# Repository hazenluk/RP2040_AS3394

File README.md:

# RP2040_AS3394
An AS3394 Voice Card controlled by RP2040.

Schematics and Routing in KiCad. Uses 30Khz PWM with 12-bit duty cycle and 1KHz Low Pass filtering to produce control voltages.

Mainly a way for me to learn and experiment with discrete Sallen-Key and MFB filters. Also a way to avoid out-of-stock DACs during the chip shortage.

Work-In-Progress photo of board:

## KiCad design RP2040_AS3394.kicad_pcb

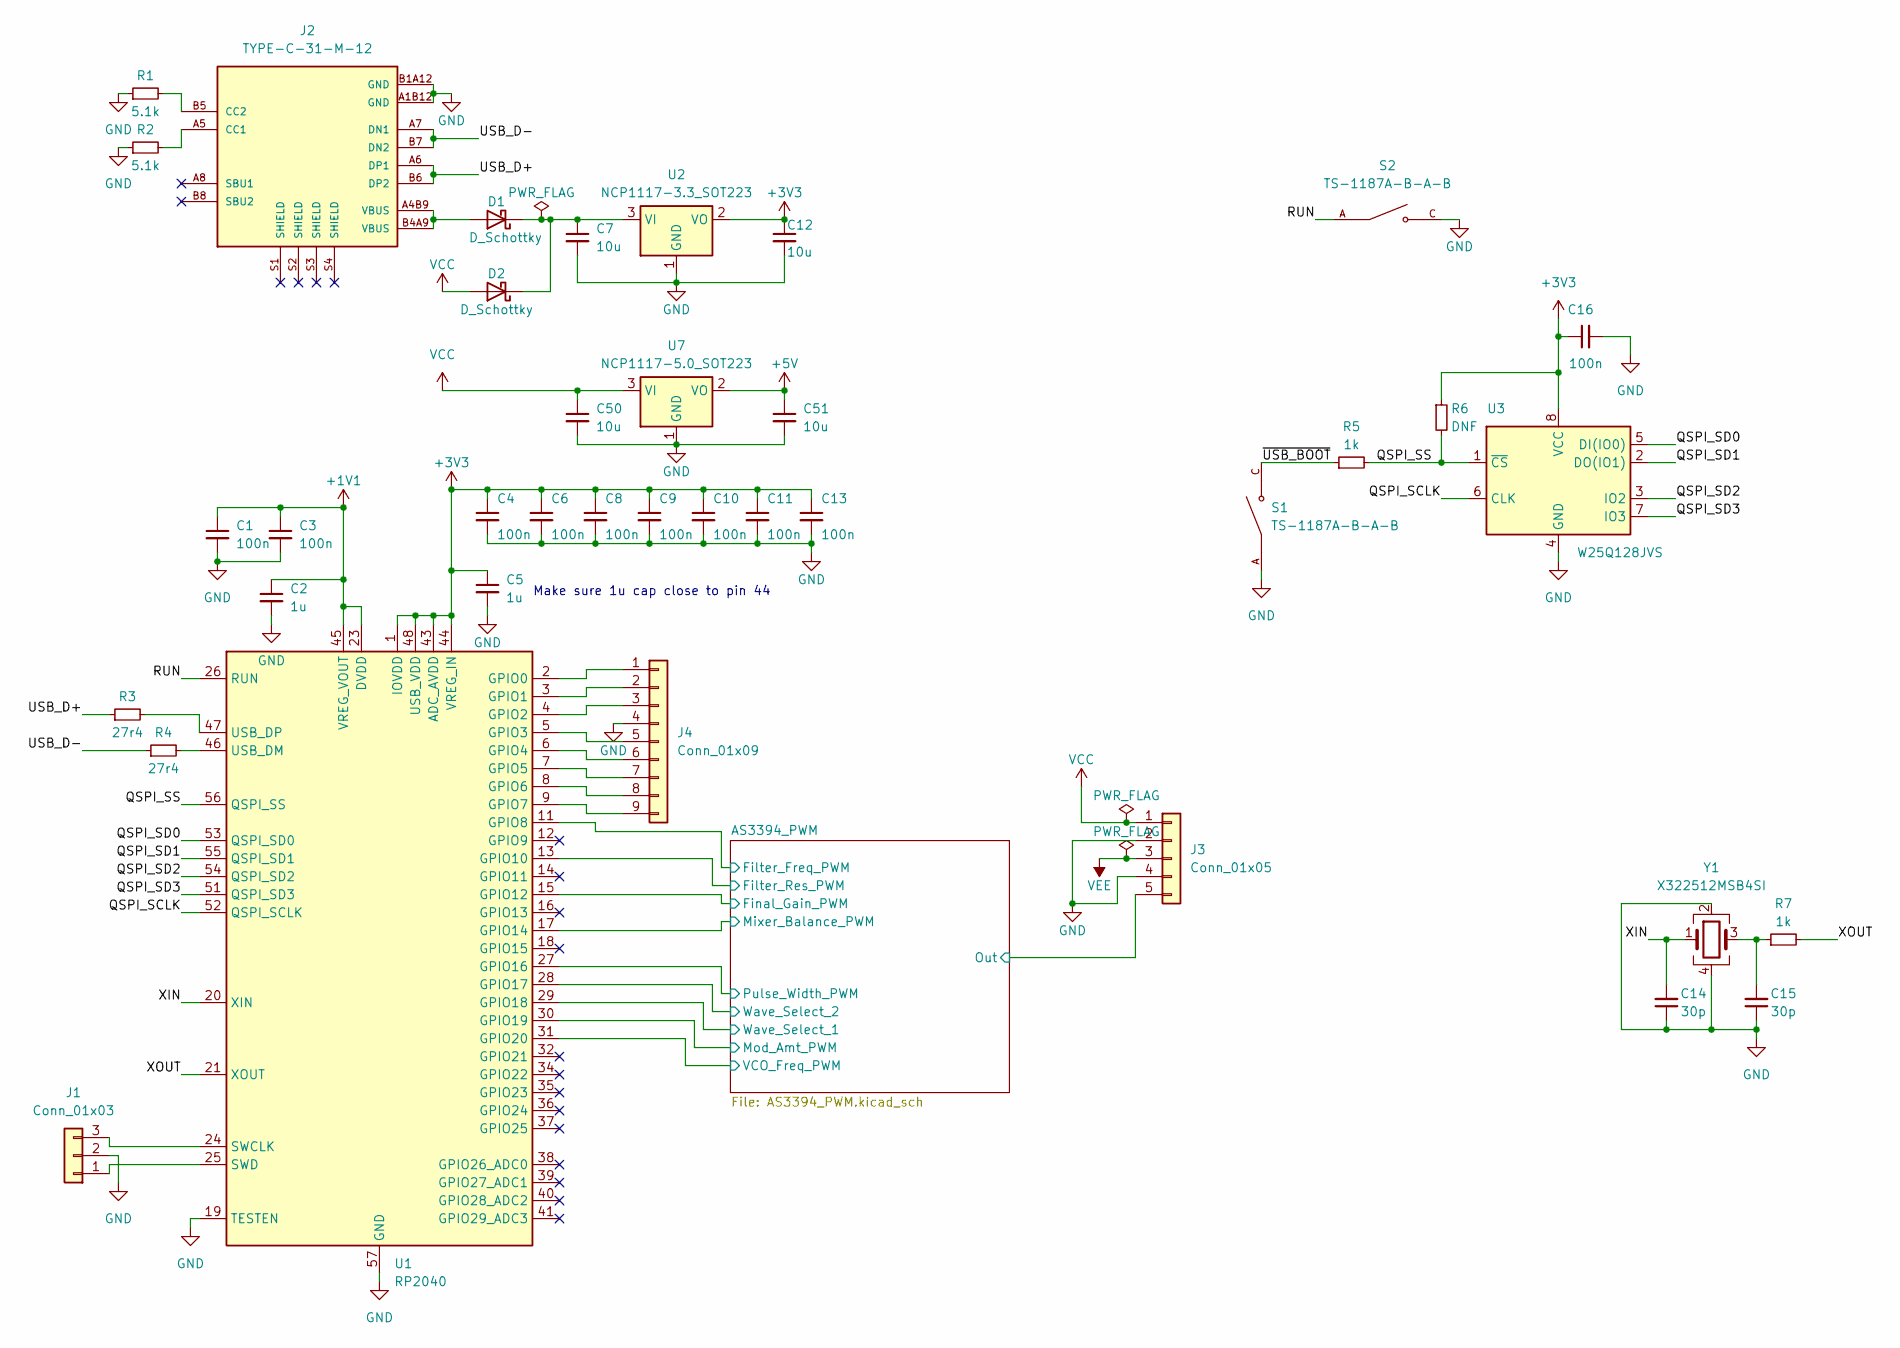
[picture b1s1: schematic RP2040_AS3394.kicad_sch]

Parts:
C1, C3, C4, C6, C8, C9, C10, C11, C13: 100n; C_0402_1005Metric
C2, C5: 1u; C_0402_1005Metric
C7, C12, C50, C51: 10u; C_0603_1608Metric
C14, C15: 30p; C_0402_1005Metric
C16: 100n; C_0603_1608Metric
D1, D2: D_Schottky; D_SMA
J1: Conn_01x03; PinHeader_1x03_P2.54mm_Vertical
J2: TYPE-C-31-M-12; HRO_TYPE-C-31-M-12; PARTREV A
J3: Conn_01x05; PinHeader_1x05_P2.54mm_Vertical
J4: Conn_01x09; PinHeader_1x09_P2.54mm_Vertical
R1, R2: 5.1k; R_0402_1005Metric
R3, R4: 27r4; R_0402_1005Metric
R5, R7: 1k; R_0402_1005Metric
R6: DNF; R_0402_1005Metric
S1, S2: TS-1187A-B-A-B; SW_TS-1187A-B-A-B; PARTREV A0
U1: RP2040; QFN-56-1EP_7x7mm_P0.4mm_EP3.2x3.2mm
U2: NCP1117-3.3_SOT223; SOT-223-3_TabPin2
U3: W25Q128JVS; SOIC-8_5.23x5.23mm_P1.27mm
U7: NCP1117-5.0_SOT223; SOT-223-3_TabPin2
Y1: X322512MSB4SI; Crystal_SMD_3225-4Pin_3.2x2.5mm

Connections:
+1V1: C1.1, C2.1, C3.1, U1.23 (DVDD), U1.45 (VREG_VOUT), U1.50 (DVDD)
+3V3: C4.1, C5.1, C6.1, C8.1, C9.1, C10.1, C11.1, C12.1, C13.1, C16.1, R6.1, U1.1 (IOVDD), U1.10 (IOVDD), U1.22 (IOVDD), U1.33 (IOVDD), U1.42 (IOVDD), U1.43 (ADC_AVDD), U1.44 (VREG_IN), U1.48 (USB_VDD), U1.49 (IOVDD), U2.2 (VO), U3.8 (VCC)
+5V: C51.1, U7.2 (VO); also elsewhere on the board
/AS3394_PWM/Filter_Freq_PWM: U1.11 (GPIO8); also elsewhere on the board
/AS3394_PWM/Filter_Res_PWM: U1.13 (GPIO10); also elsewhere on the board
/AS3394_PWM/Final_Gain_PWM: U1.15 (GPIO12); also elsewhere on the board
/AS3394_PWM/Mixer_Balance_PWM: U1.17 (GPIO14); also elsewhere on the board
/AS3394_PWM/Mod_Amt_PWM: U1.30 (GPIO19); also elsewhere on the board
/AS3394_PWM/Out: J3.5; also elsewhere on the board
/AS3394_PWM/Pulse_Width_PWM: U1.27 (GPIO16); also elsewhere on the board
/AS3394_PWM/VCO_Freq_PWM: U1.31 (GPIO20); also elsewhere on the board
/AS3394_PWM/Wave_Select_1: U1.29 (GPIO18); also elsewhere on the board
/AS3394_PWM/Wave_Select_2: U1.28 (GPIO17); also elsewhere on the board
/QSPI_SCLK: U1.52 (QSPI_SCLK), U3.6 (CLK)
/QSPI_SD0: U1.53 (QSPI_SD0), U3.5 (DI(IO0))
/QSPI_SD1: U1.55 (QSPI_SD1), U3.2 (DO(IO1))
/QSPI_SD2: U1.54 (QSPI_SD2), U3.3 (IO2)
/QSPI_SD3: U1.51 (QSPI_SD3), U3.7 (IO3)
/QSPI_SS: R5.2, R6.2, U1.56 (QSPI_SS), U3.1 (~CS)
/RUN: S2.A, S2.B, U1.26 (RUN)
/USB_D+: J2.A6 (DP1), J2.B6 (DP2), R3.1
/USB_D-: J2.A7 (DN1), J2.B7 (DN2), R4.1
/XIN: C14.2, U1.20 (XIN), Y1.1
/XOUT: R7.2, U1.21 (XOUT)
/~USB_BOOT: R5.1, S1.C, S1.D
GND: C1.2, C2.2, C3.2, C4.2, C5.2, C6.2, C7.2, C8.2, C9.2, C10.2, C11.2, C12.2, C13.2, C14.1, C15.1, C16.2, C50.2, C51.2, J1.2, J2.A1B12 (GND), J2.B1A12 (GND), J3.2, J3.4, J4.4, R1.1, R2.1, S1.A, S1.B, S2.C, S2.D, U1.19 (TESTEN), U1.57 (GND), U2.1 (GND), U3.4 (GND), U7.1 (GND), Y1.2, Y1.4; also elsewhere on the board
unnamed: C15.2, R7.1, Y1.3
unnamed: D1.2 (A), J2.A4B9 (VBUS), J2.B4A9 (VBUS)
unnamed: C7.1, D1.1 (K), D2.1 (K), U2.3 (VI)
unnamed: J1.1, U1.25 (SWD)
unnamed: J1.3, U1.24 (SWCLK)
unnamed: J2.A5 (CC1), R2.2
unnamed: J2.B5 (CC2), R1.2
unnamed: J4.1, U1.2 (GPIO0)
unnamed: J4.2, U1.3 (GPIO1)
unnamed: J4.3, U1.4 (GPIO2)
unnamed: J4.5, U1.5 (GPIO3)
unnamed: J4.6, U1.6 (GPIO4)
unnamed: J4.7, U1.7 (GPIO5)
unnamed: J4.8, U1.8 (GPIO6)
unnamed: J4.9, U1.9 (GPIO7)
unnamed: R4.2, U1.46 (USB_DM)
unnamed: R3.2, U1.47 (USB_DP)
VCC: C50.1, D2.2 (A), J3.1, U7.3 (VI); also elsewhere on the board
VEE: J3.3; also elsewhere on the board

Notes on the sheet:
Make sure 1u cap close to pin 44

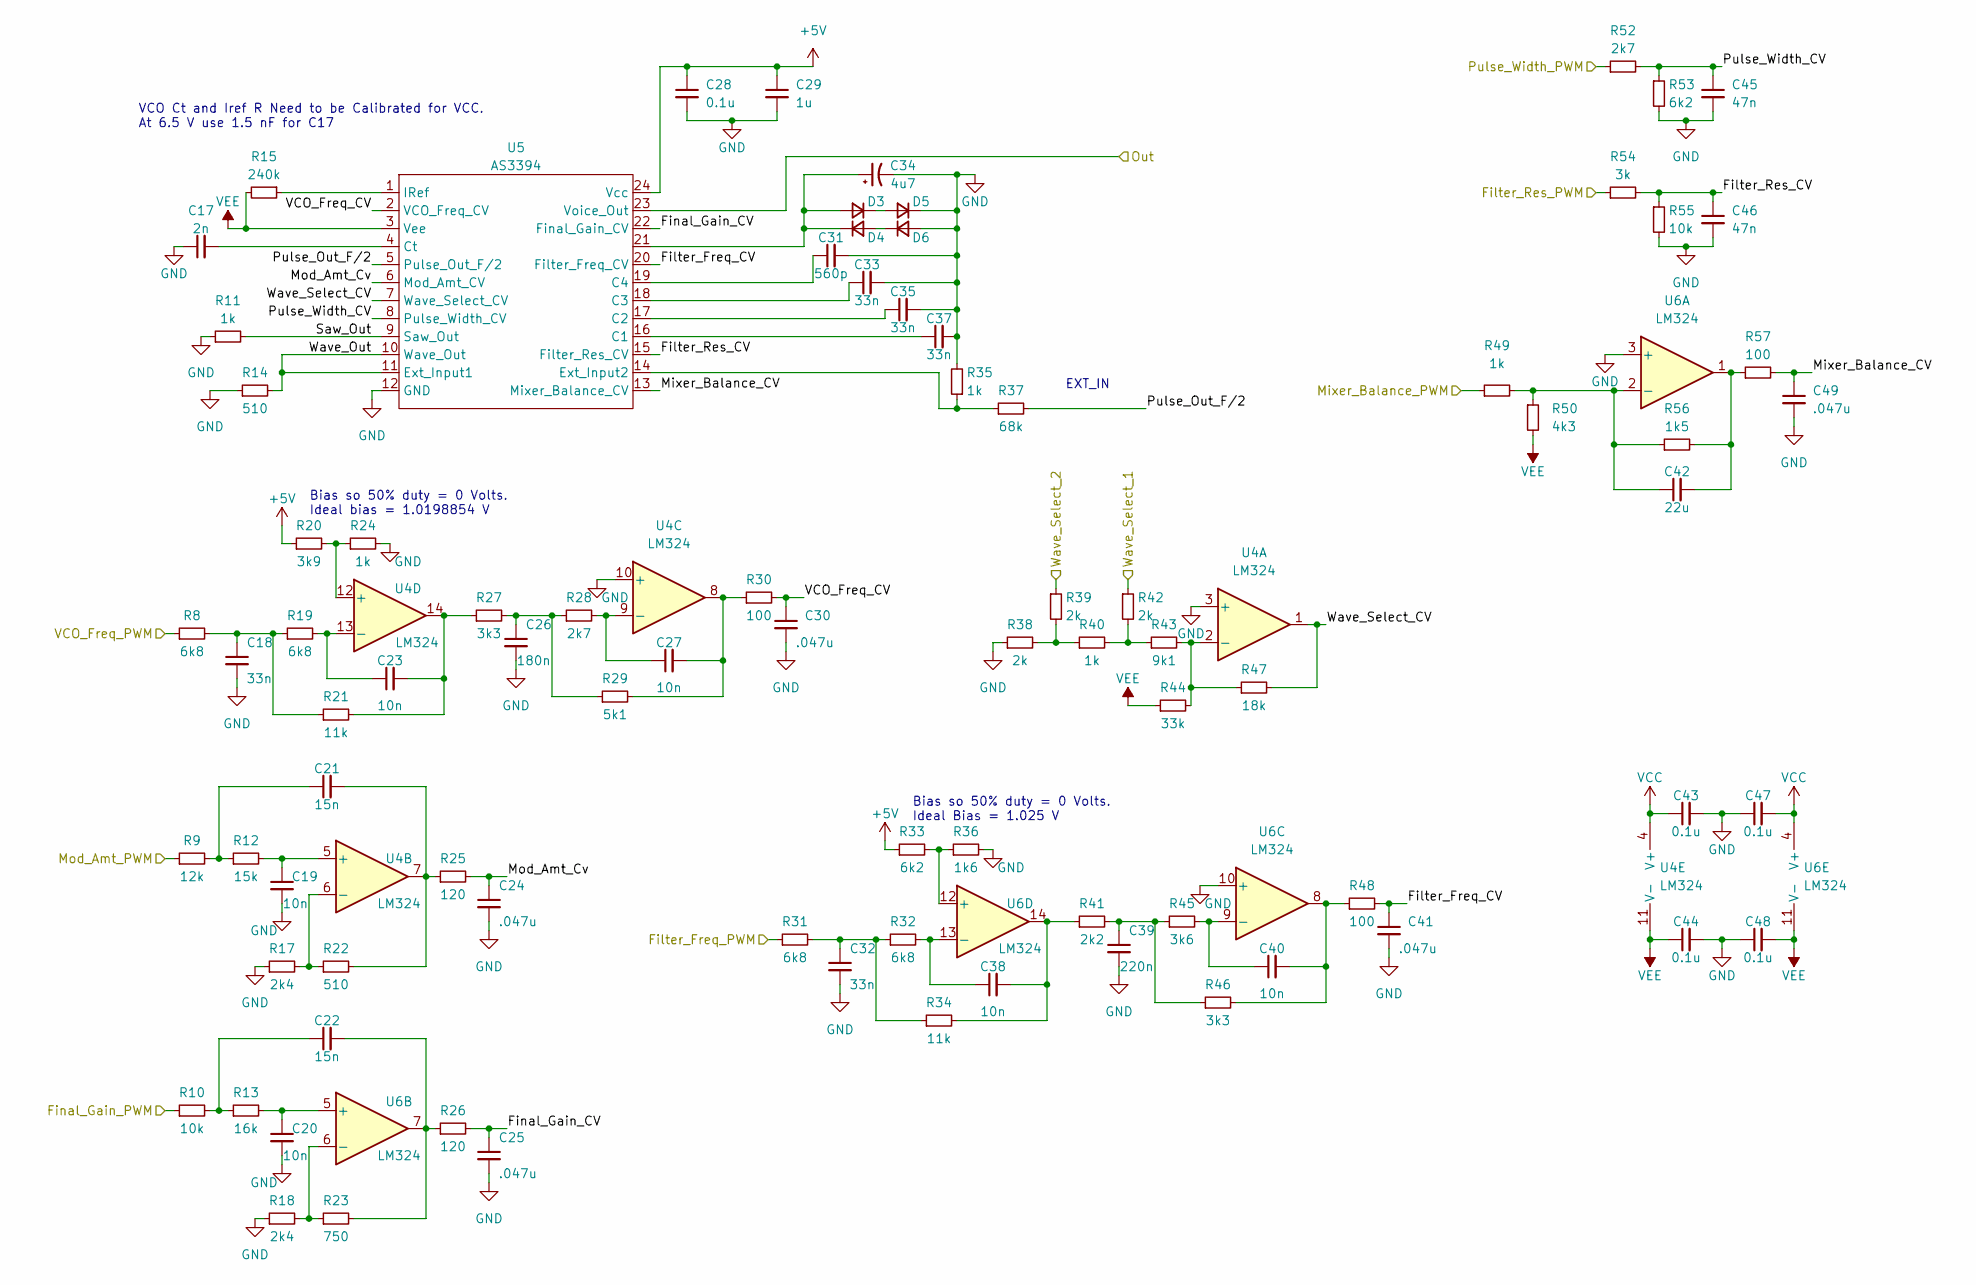
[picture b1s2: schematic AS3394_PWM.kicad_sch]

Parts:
C17: 2n; C_0603_1608Metric
C18, C32, C33, C35, C37: 33n; C_0603_1608Metric
C19, C20, C23, C27, C38, C40: 10n; C_0402_1005Metric
C21, C22: 15n; C_0603_1608Metric
C24, C25, C30, C41, C49: .047u; C_0603_1608Metric
C26: 180n; C_0805_2012Metric
C28, C43, C44, C47, C48: 0.1u; C_0402_1005Metric
C29: 1u; C_0402_1005Metric
C31: 560p; C_0402_1005Metric
C34: 4u7; CP_Elec_4x5.4
C39: 220n; C_0402_1005Metric
C42: 22u; C_1206_3216Metric
C45, C46: 47n; C_0603_1608Metric
D3, D4, D5, D6: D_Small; D_SOD-123
R8, R19, R31, R32: 6k8; R_0402_1005Metric
R9: 12k; R_0402_1005Metric
R10, R55: 10k; R_0402_1005Metric
R11, R24, R35, R40, R49: 1k; R_0402_1005Metric
R12: 15k; R_0402_1005Metric
R13: 16k; R_0805_2012Metric
R14, R22: 510; R_0402_1005Metric
R15: 240k; R_0603_1608Metric
R17, R18: 2k4; R_0402_1005Metric
R20: 3k9; R_0402_1005Metric
R21, R34: 11k; R_0603_1608Metric
R23: 750; R_0603_1608Metric
R25, R26: 120; R_0402_1005Metric
R27, R46: 3k3; R_0402_1005Metric
R28, R52: 2k7; R_0603_1608Metric
R29: 5k1; R_0402_1005Metric
R30, R48, R57: 100; R_0402_1005Metric
R33, R53: 6k2; R_0603_1608Metric
R36: 1k6; R_0402_1005Metric
R37: 68k; R_0402_1005Metric
R38, R39, R42: 2k; R_0402_1005Metric
R41: 2k2; R_0402_1005Metric
R43: 9k1; R_0603_1608Metric
R44: 33k; R_0402_1005Metric
R45: 3k6; R_0603_1608Metric
R47: 18k; R_0402_1005Metric
R50: 4k3; R_0603_1608Metric
R54: 3k; R_0603_1608Metric
R56: 1k5; R_0402_1005Metric
U4, U6: LM324; SOIC-14_3.9x8.7mm_P1.27mm
U5: AS3394; DIP-24_W7.62mm_Socket

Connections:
+5V: C28.1, C29.1, R20.1, R33.1, U5.24 (Vcc); also elsewhere on the board
/AS3394_PWM/Filter_Freq_CV: C41.1, R48.2, U5.20 (Filter_Freq_CV)
/AS3394_PWM/Filter_Freq_PWM: R31.1; also elsewhere on the board
/AS3394_PWM/Filter_Res_CV: C46.1, R54.2, R55.1, U5.15 (Filter_Res_CV)
/AS3394_PWM/Filter_Res_PWM: R54.1; also elsewhere on the board
/AS3394_PWM/Final_Gain_CV: C25.1, R26.2, U5.22 (Final_Gain_CV)
/AS3394_PWM/Final_Gain_PWM: R10.1; also elsewhere on the board
/AS3394_PWM/Mixer_Balance_CV: C49.1, R57.2, U5.13 (Mixer_Balance_CV)
/AS3394_PWM/Mixer_Balance_PWM: R49.1; also elsewhere on the board
/AS3394_PWM/Mod_Amt_Cv: C24.1, R25.2, U5.6 (Mod_Amt_CV)
/AS3394_PWM/Mod_Amt_PWM: R9.1; also elsewhere on the board
/AS3394_PWM/Out: U5.23 (Voice_Out); also elsewhere on the board
/AS3394_PWM/Pulse_Out_F/2: R37.2, U5.5 (Pulse_Out_F/2)
/AS3394_PWM/Pulse_Width_CV: C45.1, R52.2, R53.1, U5.8 (Pulse_Width_CV)
/AS3394_PWM/Pulse_Width_PWM: R52.1; also elsewhere on the board
/AS3394_PWM/Saw_Out: R11.2, U5.9 (Saw_Out)
/AS3394_PWM/VCO_Freq_CV: C30.1, R30.2, U5.2 (VCO_Freq_CV)
/AS3394_PWM/VCO_Freq_PWM: R8.1; also elsewhere on the board
/AS3394_PWM/Wave_Out: R14.2, U5.10 (Wave_Out), U5.11 (Ext_Input1)
/AS3394_PWM/Wave_Select_1: R42.1; also elsewhere on the board
/AS3394_PWM/Wave_Select_2: R39.1; also elsewhere on the board
/AS3394_PWM/Wave_Select_CV: R47.2, U4.1, U5.7 (Wave_Select_CV)
GND: C17.1, C18.2, C19.2, C20.2, C24.2, C25.2, C26.2, C28.2, C29.2, C30.2, C31.2, C32.2, C33.2, C34.2, C35.2, C37.2, C39.2, C41.2, C43.2, C44.2, C45.2, C46.2, C47.1, C48.1, C49.2, D5.1 (K), D6.2 (A), R11.1, R14.1, R17.1, R18.1, R24.2, R35.2, R36.2, R38.1, R53.2, R55.2, U4.3 (+), U4.10 (+), U5.12 (GND), U6.3 (+), U6.10 (+); also elsewhere on the board
unnamed: C18.1, R8.2, R19.1, R21.1
unnamed: C21.1, R9.2, R12.1
unnamed: C21.2, R22.2, R25.1, U4.7
unnamed: C22.1, R10.2, R13.1
unnamed: C22.2, R23.2, R26.1, U6.7
unnamed: C23.2, R21.2, R27.1, U4.14
unnamed: C26.1, R27.2, R28.1, R29.1
unnamed: C27.2, R29.2, R30.1, U4.8
unnamed: C32.1, R31.2, R32.1, R34.1
unnamed: C38.2, R34.2, R41.1, U6.14
unnamed: C39.1, R41.2, R45.1, R46.1
unnamed: C40.2, R46.2, R48.1, U6.8
unnamed: C42.2, R56.2, R57.1, U6.1
unnamed: C34.1, D3.2 (A), D4.1 (K), U5.21
unnamed: D3.1 (K), D5.2 (A)
unnamed: D4.2 (A), D6.1 (K)
unnamed: R38.2, R39.2, R40.1
unnamed: R40.2, R42.2, R43.1
unnamed: R43.2, R44.2, R47.1, U4.2 (-)
unnamed: C19.1, R12.2, U4.5 (+)
unnamed: R17.2, R22.1, U4.6 (-)
unnamed: C27.1, R28.2, U4.9 (-)
unnamed: R20.2, R24.1, U4.12 (+)
unnamed: C23.1, R19.2, U4.13 (-)
unnamed: C37.1, U5.16 (C1)
unnamed: C35.1, U5.17 (C2)
unnamed: C33.1, U5.18 (C3)
unnamed: C31.1, U5.19 (C4)
unnamed: C17.2, U5.4 (Ct)
unnamed: R35.1, R37.1, U5.14 (Ext_Input2)
unnamed: R15.1, U5.1 (IRef)
unnamed: C42.1, R49.2, R50.1, R56.1, U6.2 (-)
unnamed: C20.1, R13.2, U6.5 (+)
unnamed: R18.2, R23.1, U6.6 (-)
unnamed: C40.1, R45.2, U6.9 (-)
unnamed: R33.2, R36.1, U6.12 (+)
unnamed: C38.1, R32.2, U6.13 (-)
VCC: C43.1, C47.2, U4.4 (V+), U6.4 (V+); also elsewhere on the board
VEE: C44.1, C48.2, R15.2, R44.1, R50.2, U4.11 (V-), U5.3 (Vee), U6.11 (V-); also elsewhere on the board

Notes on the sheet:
Bias so 50% duty = 0 Volts. Ideal Bias = 1.025 V
EXT_IN
Bias so 50% duty = 0 Volts. Ideal bias = 1.0198854 V
VCO Ct and Iref R Need to be Calibrated for VCC. At 6.5 V use 1.5 nF for C17

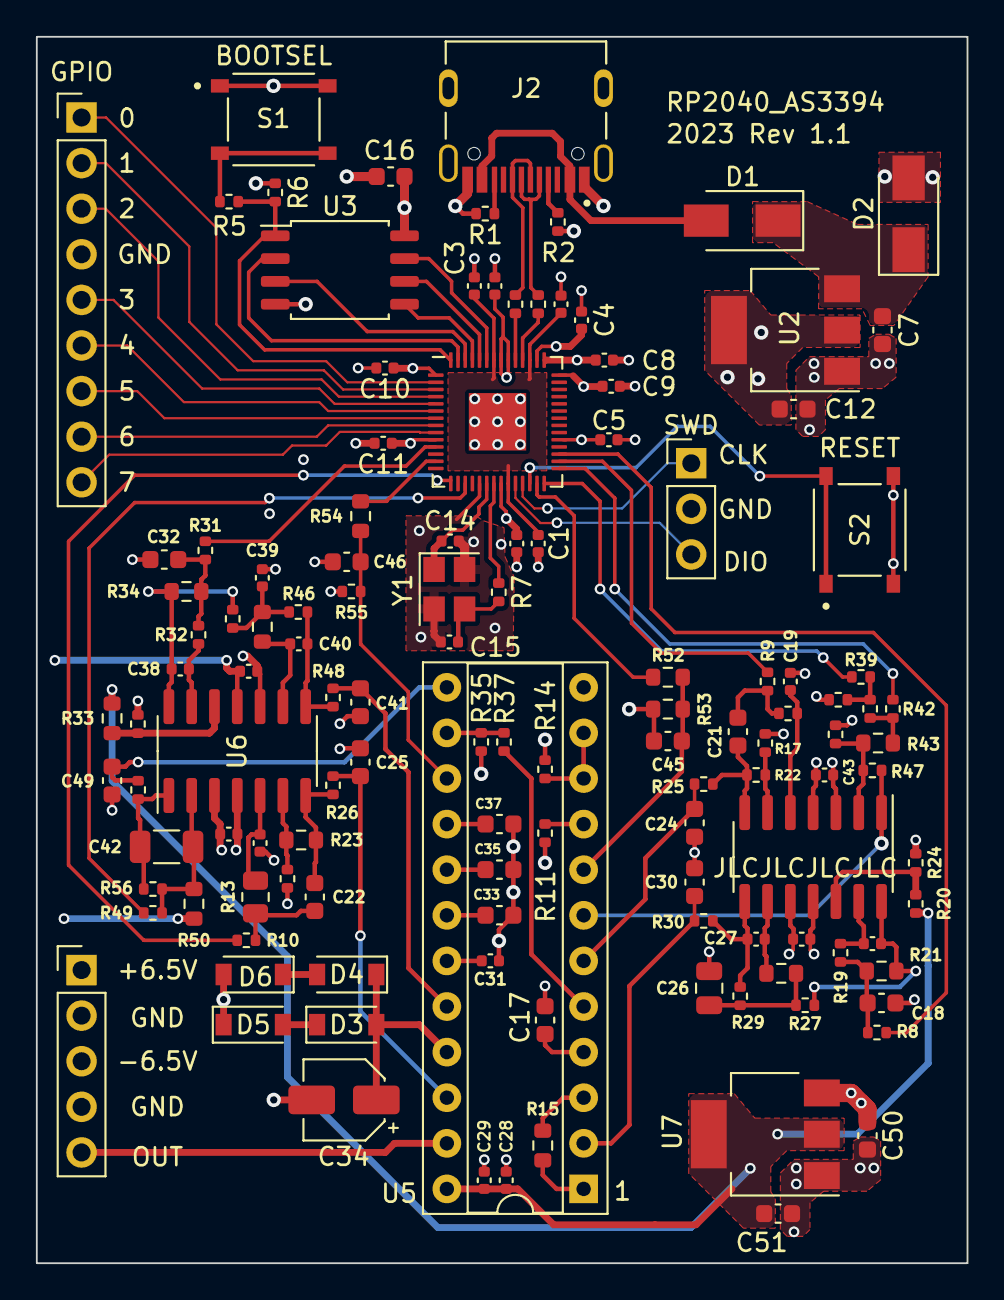
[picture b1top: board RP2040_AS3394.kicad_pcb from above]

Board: 4 copper layers, 51.8 x 68.3 mm, 125 parts (0 on the bottom side), 93 nets.

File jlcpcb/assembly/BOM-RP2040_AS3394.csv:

Comment,Designator,Footprint,LCSC
120R,FB1,L_0805_2012Metric,C1015
TL071,U7,SOIC-8_3.9x4.9mm_P1.27mm,C107648
1k,"R11,R35,R40,R49,R5,R7",R_0402_1005Metric,C11702
22u,C42,C_1206_3216Metric,C12891
2k7,"R28,R52",R_0603_1608Metric,C13167
100n,C16,C_0603_1608Metric,C14663
NCP1117-3.3_SOT223,U2,SOT-223-3_TabPin2,C146799
10n,"C19,C20,C23,C27,C28,C38,C40",C_0402_1005Metric,C15195
0.1u,"C43,C44,C47,C48,C50,C51",C_0402_1005Metric,C1525
47p,C52,C_0402_1005Metric,C1567
30p,"C14,C15",C_0402_1005Metric,C1570
1n5,C17,C_0603_1608Metric,C1595
15n,"C21,C22",C_0603_1608Metric,C1596
47n,"C45,C46",C_0603_1608Metric,C1622
.047u,"C24,C25,C30,C41,C49",C_0603_1608Metric,C1623
TYPE-C-31-M-12,J2,HRO_TYPE-C-31-M-12,C165948
220n,C39,C_0402_1005Metric,C16772
16k,R13,R_0805_2012Metric,C17490
RP2040,U1,QFN-56-1EP_7x7mm_P0.4mm_EP3.2x3.2mm,C2040
33n,"C18,C32,C33,C35,C37",C_0603_1608Metric,C21117
D_Schottky,"D1,D2",D_SMA,C22452
3k6,R45,R_0603_1608Metric,C22980
4k3,R50,R_0603_1608Metric,C23159
560,R24,R_0603_1608Metric,C23204
750,R23,R_0603_1608Metric,C23241
9k1,R43,R_0603_1608Metric,C23260
100,"R30,R48,R57",R_0402_1005Metric,C25076
120,"R25,R26",R_0402_1005Metric,C25079
4u7,C34,CP_Elec_4x5.4,C250890
300,R36,R_0402_1005Metric,C25102
510,"R14,R22",R_0402_1005Metric,C25123
10k,"R10,R55",R_0402_1005Metric,C25744
12k,R9,R_0402_1005Metric,C25752
15k,R12,R_0402_1005Metric,C25756
18k,R47,R_0402_1005Metric,C25762
33k,R44,R_0402_1005Metric,C25779
1k5,R56,R_0402_1005Metric,C25867
2k2,R41,R_0402_1005Metric,C25879
2k4,"R17,R18",R_0402_1005Metric,C25882
3k3,"R27,R46",R_0402_1005Metric,C25890
5.1k,"R1,R2,R29",R_0402_1005Metric,C25905
6k8,"R19,R31,R32,R8",R_0402_1005Metric,C25917
7.5k,R16,R_0402_1005Metric,C25918
1k6,R33,R_0402_1005Metric,C25931
11k,"R21,R34",R_0603_1608Metric,C25950
100n,"C1,C10,C11,C13,C3,C4,C6,C8,C9",C_0402_1005Metric,C307331
27r4,"R3,R4",R_0402_1005Metric,C31439
560p,C31,C_0402_1005Metric,C318606
TS-1187A-B-A-B,"S1,S2",SW_TS-1187A-B-A-B,C318884
68k,R37,R_0402_1005Metric,C36871
2k,"R38,R39,R42",R_0402_1005Metric,C4109
240k,R15,R_0603_1608Metric,C4197
3k,"R20,R54",R_0603_1608Metric,C4211
6k2,R53,R_0603_1608Metric,C4260
1u,"C2,C29,C36,C5",C_0402_1005Metric,C52923
180n,C26,C_0805_2012Metric,C67952
LM324,"U4,U6",SOIC-14_3.9x8.7mm_P1.27mm,C71035
X322512MSB4SI,Y1,Crystal_SMD_3225-4Pin_3.2x2.5mm,C9002
D_Small,"D3,D4,D5,D6",D_SMA,C95872
10u,"C12,C7",C_0603_1608Metric,C96446
W25Q128JVS,U3,SOIC-8_5.23x5.23mm_P1.27mm,C97521
DNF,R6,R_0402_1005Metric,
Conn_01x08,J4,PinHeader_1x08_P2.54mm_Vertical,
AS3394,U5,DIP-24_W7.62mm_Socket,
Conn_01x03,J1,PinHeader_1x03_P2.54mm_Vertical,
Conn_01x02,J3,PinHeader_1x02_P2.54mm_Vertical,
Conn_01x03,J5,PinHeader_1x03_P2.54mm_Vertical,

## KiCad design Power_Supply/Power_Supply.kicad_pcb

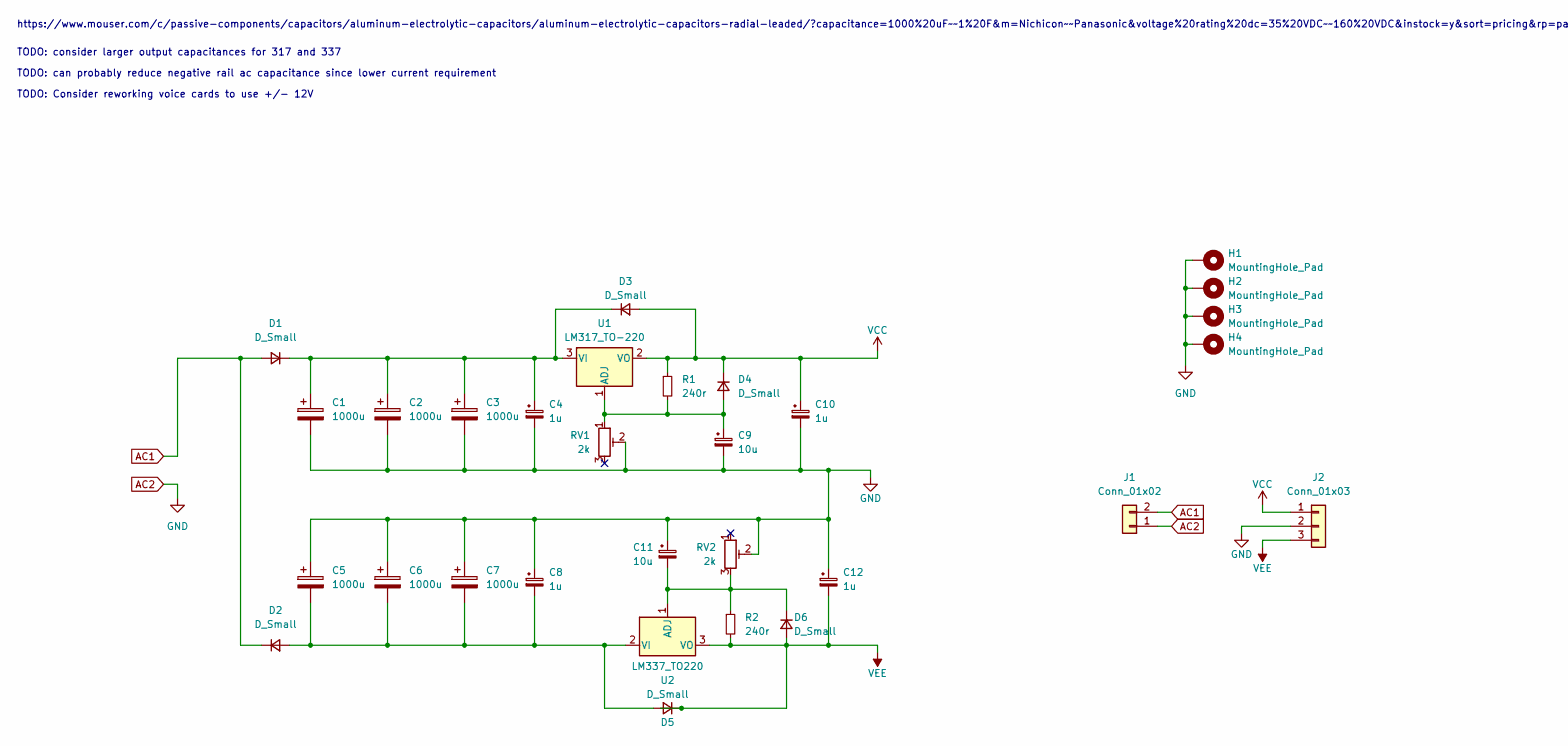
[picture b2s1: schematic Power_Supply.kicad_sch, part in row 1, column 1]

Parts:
C1, C2, C3, C5, C6, C7: 1000u; CP_Radial_D16.0mm_P7.50mm
C4, C8, C10, C12: 1u; C_Rect_L4.6mm_W2.0mm_P2.50mm_MKS02_FKP02
C9, C11: 10u; CP_Radial_D6.3mm_P2.50mm
D1, D2, D3, D4, D5, D6: D_Small; D_DO-41_SOD81_P7.62mm_Horizontal
H1, H2, H3, H4: MountingHole_Pad; MountingHole_3.2mm_M3_DIN965_Pad
J1: Conn_01x02; PinHeader_1x02_P2.54mm_Vertical
J2: Conn_01x03; PinHeader_1x03_P2.54mm_Vertical
R1, R2: 240r; R_Axial_DIN0204_L3.6mm_D1.6mm_P7.62mm_Horizontal
RV1, RV2: 2k; Potentiometer_Runtron_RM-065_Vertical
U1: LM317_TO-220; TO-220-3_Vertical
U2: LM337_TO220; TO-220-3_Vertical

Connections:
AC1: D1.2 (A), D2.1 (K), J1.2
AC2: C1.2, C2.2, C3.2, C4.2, C5.1, C6.1, C7.1, C8.1, C9.2, C10.2, C11.1, C12.1, H1.1, H2.1, H3.1, H4.1, J1.1, J2.2, RV1.2, RV2.2
unnamed: C1.1, C2.1, C3.1, C4.1, D1.1 (K), D3.1 (K), U1.3 (VI)
unnamed: C5.2, C6.2, C7.2, C8.2, D2.2 (A), D5.2 (A), U2.2 (VI)
unnamed: C9.1, D4.2 (A), R1.2, RV1.1, U1.1 (ADJ)
unnamed: C11.2, D6.1 (K), R2.1, RV2.3, U2.1 (ADJ)
VCC: C10.1, D3.2 (A), D4.1 (K), J2.1, R1.1, U1.2 (VO)
VEE: C12.2, D5.1 (K), D6.2 (A), J2.3, R2.2, U2.3 (VO)

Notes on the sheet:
TODO: consider larger output capacitances for 317 and 337
https://www.mouser.com/c/passive-components/capacitors/aluminum-electrolytic-capacitors/aluminum-electrolytic-capacitors-radial-leaded/?capacitance=1000%20uF~~1%20F&m=Nichicon~~Panasonic&voltage%20rating%20dc=35%20VDC~~160%20VDC&instock=y&sort=pricing&rp=passive-components%2Fcapacitors%2Faluminum-e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
TODO: can probably reduce negative rail ac capacitance since lower current requirement
TODO: Consider reworking voice cards to use +/- 12V

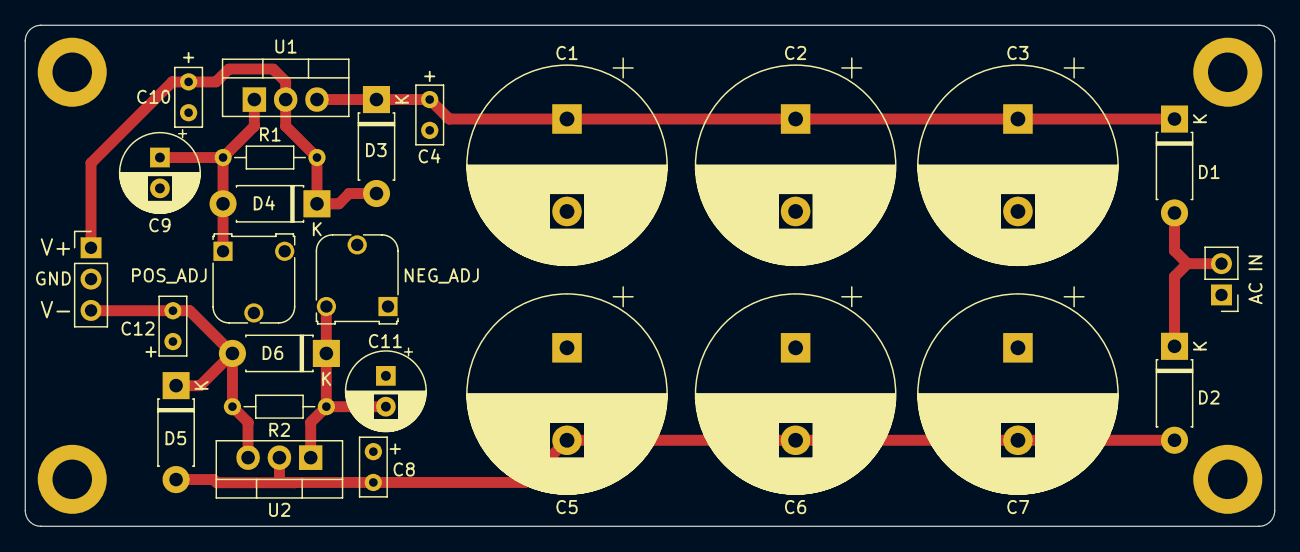
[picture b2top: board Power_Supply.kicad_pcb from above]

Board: 2 copper layers, 101.3 x 40.6 mm, 30 parts (0 on the bottom side), 8 nets.

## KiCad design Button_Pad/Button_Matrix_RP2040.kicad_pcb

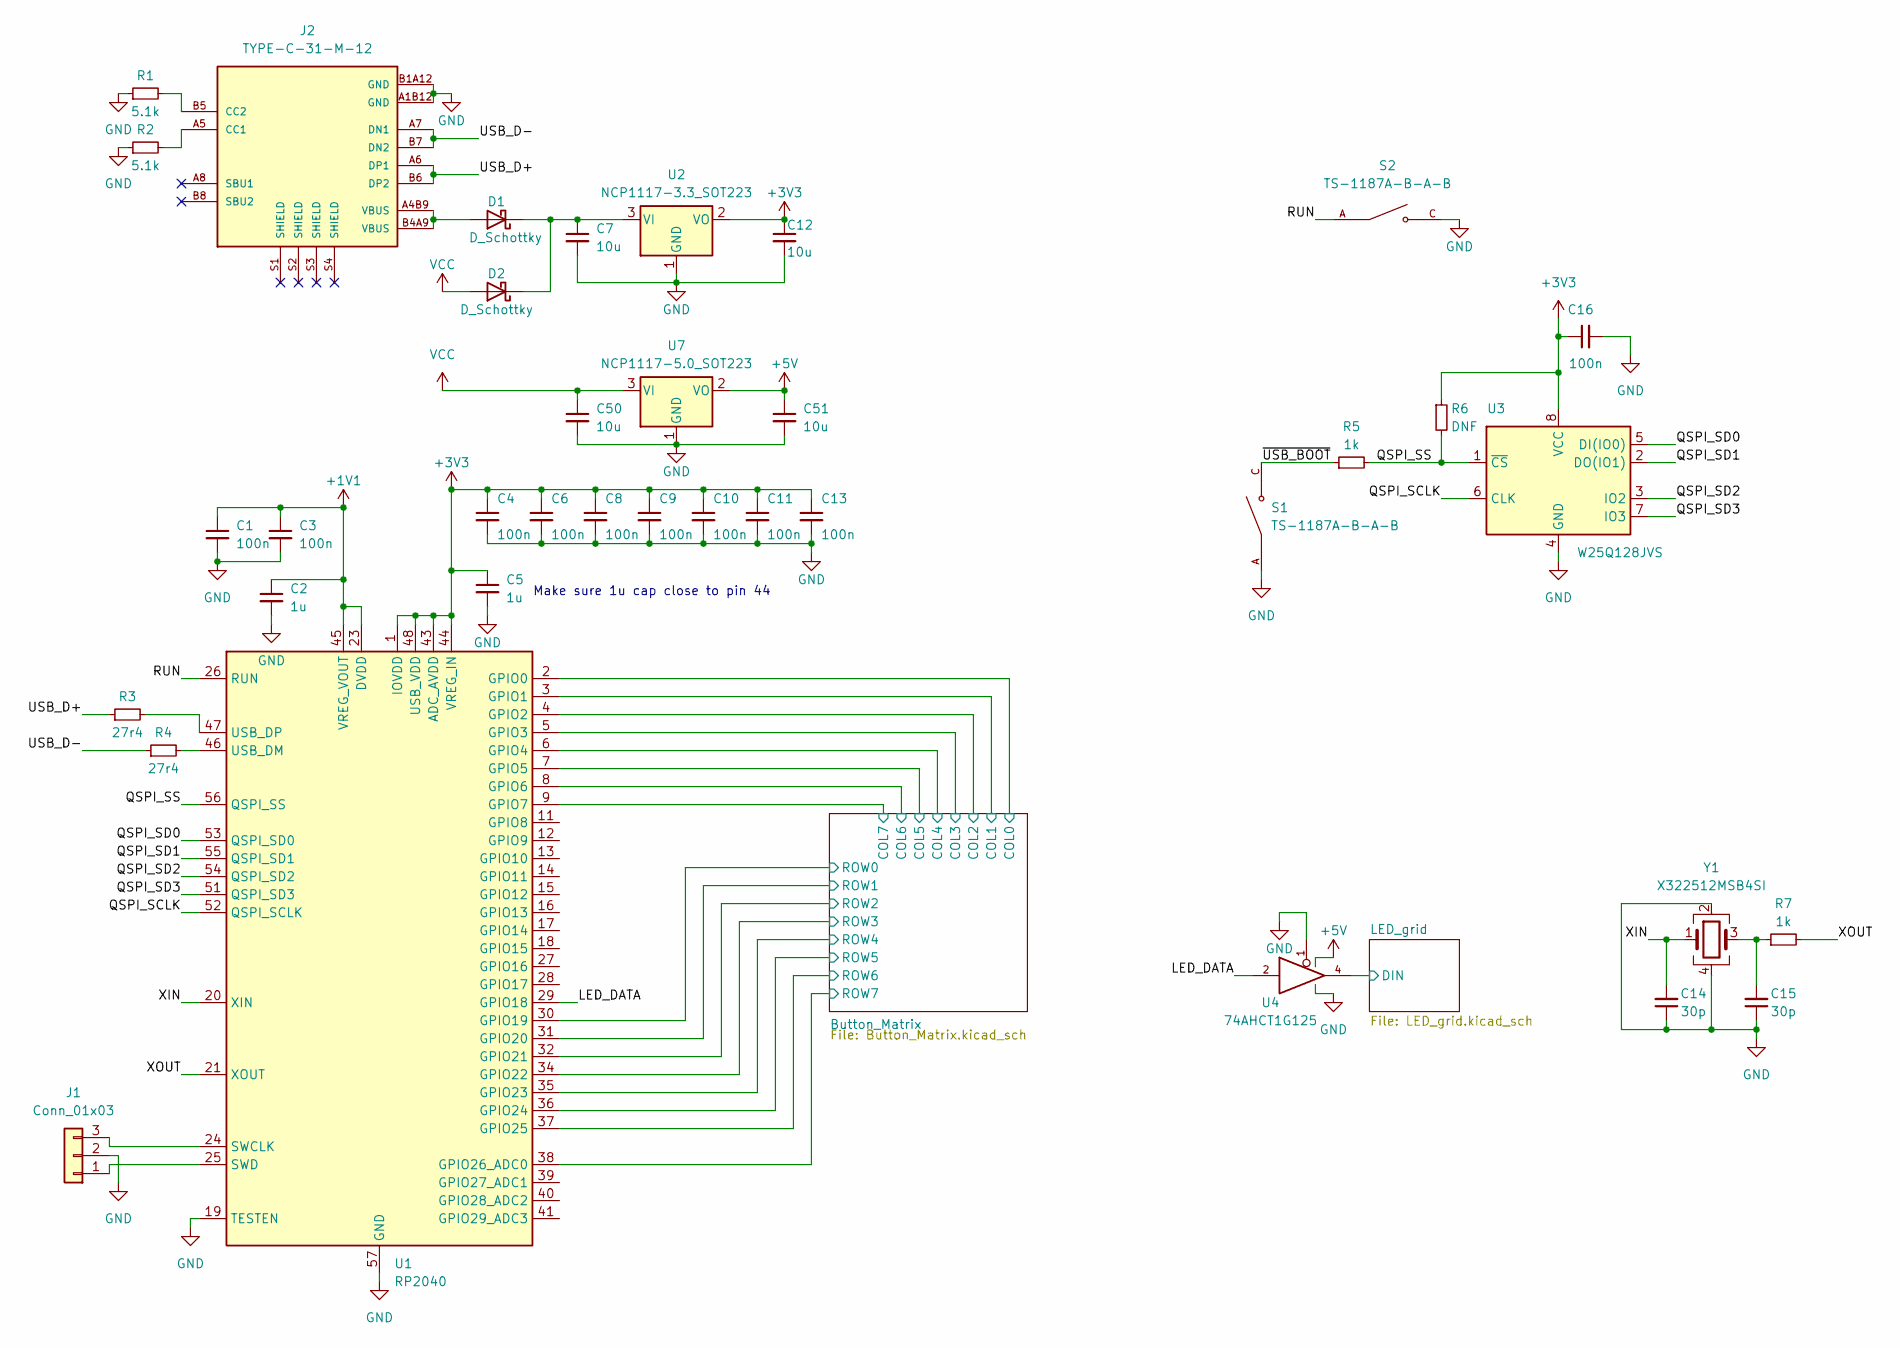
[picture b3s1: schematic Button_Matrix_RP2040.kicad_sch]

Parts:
C1, C3, C4, C6, C8, C9, C10, C11, C13: 100n; C_0402_1005Metric
C2, C5: 1u; C_0402_1005Metric
C7, C12, C50, C51: 10u; C_0603_1608Metric
C14, C15: 30p; C_0402_1005Metric
C16: 100n; C_0603_1608Metric
D1, D2: D_Schottky; D_SMA
J1: Conn_01x03; PinHeader_1x03_P2.54mm_Vertical
J2: TYPE-C-31-M-12; HRO_TYPE-C-31-M-12; PARTREV A
R1, R2: 5.1k; R_0402_1005Metric
R3, R4: 27r4; R_0402_1005Metric
R5, R7: 1k; R_0402_1005Metric
R6: DNF; R_0402_1005Metric
S1, S2: TS-1187A-B-A-B; SW_TS-1187A-B-A-B; PARTREV A0
U1: RP2040; QFN-56-1EP_7x7mm_P0.4mm_EP3.2x3.2mm
U2: NCP1117-3.3_SOT223; SOT-223-3_TabPin2
U3: W25Q128JVS; SOIC-8_5.23x5.23mm_P1.27mm
U4: 74AHCT1G125; SOT-23-5
U7: NCP1117-5.0_SOT223; SOT-223-3_TabPin2
Y1: X322512MSB4SI; Crystal_SMD_3225-4Pin_3.2x2.5mm

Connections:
+1V1: C1.1, C2.1, C3.1, U1.23 (DVDD), U1.45 (VREG_VOUT), U1.50 (DVDD)
+3V3: C4.1, C5.1, C6.1, C8.1, C9.1, C10.1, C11.1, C12.1, C13.1, C16.1, R6.1, U1.1 (IOVDD), U1.10 (IOVDD), U1.22 (IOVDD), U1.33 (IOVDD), U1.42 (IOVDD), U1.43 (ADC_AVDD), U1.44 (VREG_IN), U1.48 (USB_VDD), U1.49 (IOVDD), U2.2 (VO), U3.8 (VCC)
/Button_Matrix/COL0: U1.2 (GPIO0); also elsewhere on the board
/Button_Matrix/COL1: U1.3 (GPIO1); also elsewhere on the board
/Button_Matrix/COL2: U1.4 (GPIO2); also elsewhere on the board
/Button_Matrix/COL3: U1.5 (GPIO3); also elsewhere on the board
/Button_Matrix/COL4: U1.6 (GPIO4); also elsewhere on the board
/Button_Matrix/COL5: U1.7 (GPIO5); also elsewhere on the board
/Button_Matrix/COL6: U1.8 (GPIO6); also elsewhere on the board
/Button_Matrix/COL7: U1.9 (GPIO7); also elsewhere on the board
/Button_Matrix/ROW0: U1.30 (GPIO19); also elsewhere on the board
/Button_Matrix/ROW1: U1.31 (GPIO20); also elsewhere on the board
/Button_Matrix/ROW2: U1.32 (GPIO21); also elsewhere on the board
/Button_Matrix/ROW3: U1.34 (GPIO22); also elsewhere on the board
/Button_Matrix/ROW4: U1.35 (GPIO23); also elsewhere on the board
/Button_Matrix/ROW5: U1.36 (GPIO24); also elsewhere on the board
/Button_Matrix/ROW6: U1.37 (GPIO25); also elsewhere on the board
/Button_Matrix/ROW7: U1.38 (GPIO26_ADC0); also elsewhere on the board
/LED_DATA: U1.29 (GPIO18), U4.2
/LED_grid/DIN: U4.4; also elsewhere on the board
/QSPI_SCLK: U1.52 (QSPI_SCLK), U3.6 (CLK)
/QSPI_SD0: U1.53 (QSPI_SD0), U3.5 (DI(IO0))
/QSPI_SD1: U1.55 (QSPI_SD1), U3.2 (DO(IO1))
/QSPI_SD2: U1.54 (QSPI_SD2), U3.3 (IO2)
/QSPI_SD3: U1.51 (QSPI_SD3), U3.7 (IO3)
/QSPI_SS: R5.2, R6.2, U1.56 (QSPI_SS), U3.1 (~CS)
/RUN: S2.A, S2.B, U1.26 (RUN)
/USB_D+: J2.A6 (DP1), J2.B6 (DP2), R3.1
/USB_D-: J2.A7 (DN1), J2.B7 (DN2), R4.1
/XIN: C14.2, U1.20 (XIN), Y1.1
/XOUT: R7.2, U1.21 (XOUT)
/~USB_BOOT: R5.1, S1.C, S1.D
GND: C1.2, C2.2, C3.2, C4.2, C5.2, C6.2, C7.2, C8.2, C9.2, C10.2, C11.2, C12.2, C13.2, C14.1, C15.1, C16.2, C50.2, C51.2, J1.2, J2.A1B12 (GND), J2.B1A12 (GND), R1.1, R2.1, S1.A, S1.B, S2.C, S2.D, U1.19 (TESTEN), U1.57 (GND), U2.1 (GND), U3.4 (GND), U4.1, U4.3 (GND), U7.1 (GND), Y1.2, Y1.4; also elsewhere on the board
unnamed: C7.1, D1.1 (K), D2.1 (K), U2.3 (VI)
unnamed: C15.2, R7.1, Y1.3
unnamed: D1.2 (A), J2.A4B9 (VBUS), J2.B4A9 (VBUS)
unnamed: J1.1, U1.25 (SWD)
unnamed: J1.3, U1.24 (SWCLK)
unnamed: J2.A5 (CC1), R2.2
unnamed: J2.B5 (CC2), R1.2
unnamed: R3.2, U1.47 (USB_DP)
unnamed: R4.2, U1.46 (USB_DM)

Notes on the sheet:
Make sure 1u cap close to pin 44
